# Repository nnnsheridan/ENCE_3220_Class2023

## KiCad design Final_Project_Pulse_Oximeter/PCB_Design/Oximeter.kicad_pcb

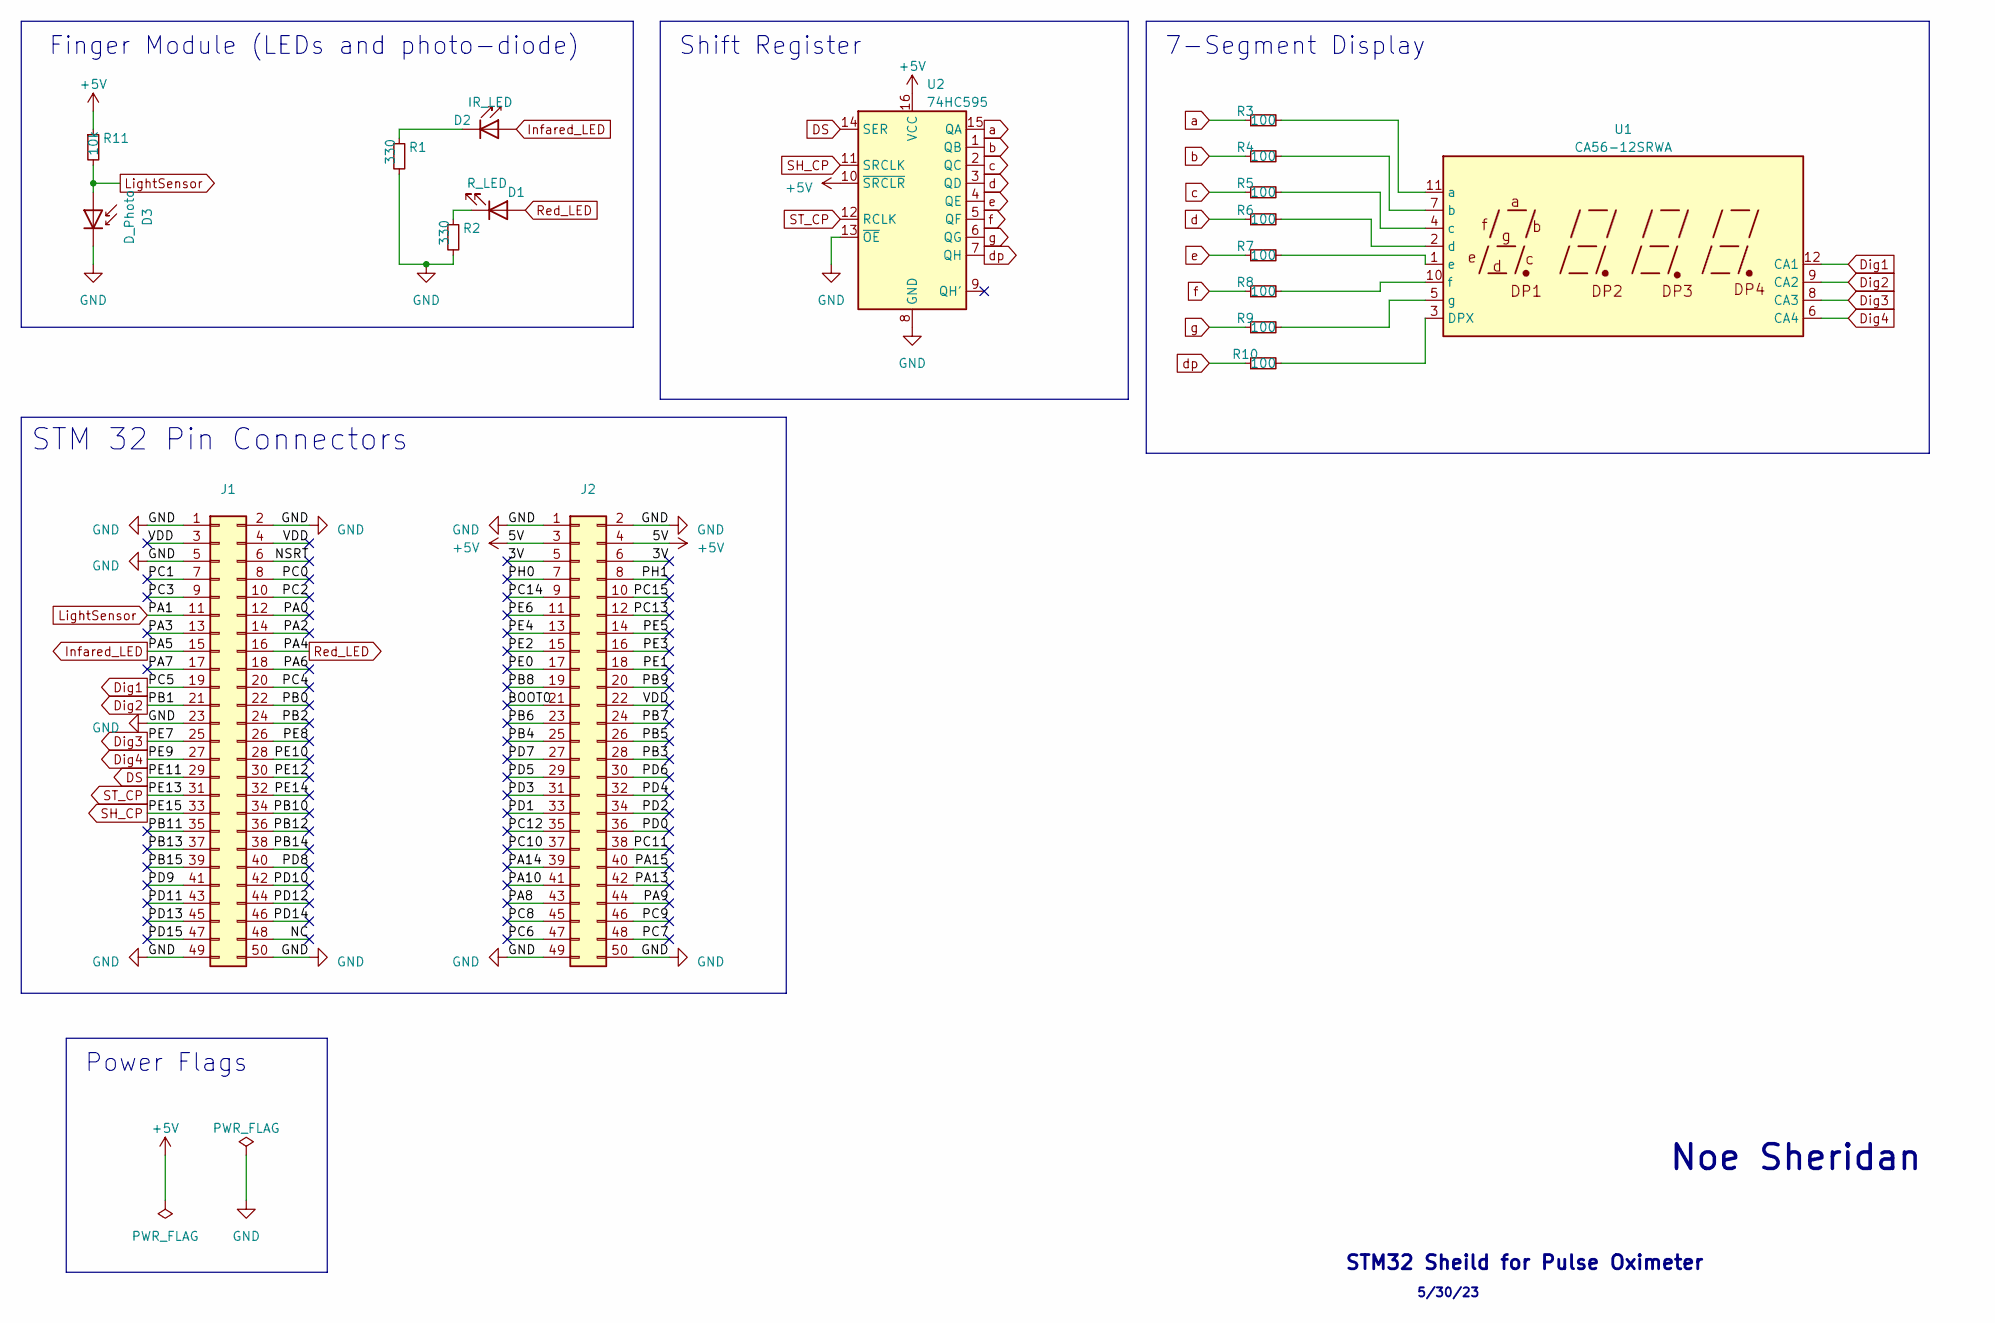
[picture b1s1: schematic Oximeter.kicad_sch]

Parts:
D1: R_LED; LED_D3.0mm
D2: IR_LED; LED_D3.0mm_IRGrey
D3: D_Photo; LED_D3.0mm_IRBlack
J1, J2: Conn_02x25_Odd_Even; PinSocket_2x25_P2.54mm_Vertical
R1, R2: 330; R_0805_2012Metric
R3, R4, R5, R6, R7, R8, R9, R10: 100; R_0805_2012Metric
R11: 10k; R_0805_2012Metric
U1: CA56-12SRWA
U2: 74HC595; HTSSOP-16-1EP_4.4x5mm_P0.65mm_EP3.4x5mm

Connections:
+5V: J2.3, J2.4, R11.1, U2.10 (~SRCLR), U2.16 (VCC)
/3V: J2.5, J2.6
/BOOT0: J2.21
/NC: J1.48
/NSRT: J1.6
/PA0: J1.12
/PA2: J1.14
/PA3: J1.13
/PA6: J1.18
/PA7: J1.17
/PA8: J2.43
/PA9: J2.44
/PA10: J2.41
/PA13: J2.42
/PA14: J2.39
/PA15: J2.40
/PB0: J1.22
/PB2: J1.24
/PB3: J2.28
/PB4: J2.25
/PB5: J2.26
/PB6: J2.23
/PB7: J2.24
/PB8: J2.19
/PB9: J2.20
/PB10: J1.34
/PB11: J1.35
/PB12: J1.36
/PB13: J1.37
/PB14: J1.38
/PB15: J1.39
/PC0: J1.8
/PC1: J1.7
/PC2: J1.10
/PC3: J1.9
/PC4: J1.20
/PC6: J2.47
/PC7: J2.48
/PC8: J2.45
/PC9: J2.46
/PC10: J2.37
/PC11: J2.38
/PC12: J2.35
/PC13: J2.12
/PC14: J2.9
/PC15: J2.10
/PD0: J2.36
/PD1: J2.33
/PD2: J2.34
/PD3: J2.31
/PD4: J2.32
/PD5: J2.29
/PD6: J2.30
/PD7: J2.27
/PD8: J1.40
/PD9: J1.41
/PD10: J1.42
/PD11: J1.43
/PD12: J1.44
/PD13: J1.45
/PD14: J1.46
/PD15: J1.47
/PE0: J2.17
/PE1: J2.18
/PE2: J2.15
/PE3: J2.16
/PE4: J2.13
/PE5: J2.14
/PE6: J2.11
/PE8: J1.26
/PE10: J1.28
/PE12: J1.30
/PE14: J1.32
/PH0: J2.7
/PH1: J2.8
/VDD: J1.3, J1.4, J2.22
DS: J1.29, U2.14 (SER)
Dig1: J1.19, U1.12 (CA1)
Dig2: J1.21, U1.9 (CA2)
Dig3: J1.25, U1.8 (CA3)
Dig4: J1.27, U1.6 (CA4)
GND: D3.1 (K), J1.1, J1.2, J1.5, J1.23, J1.49, J1.50, J2.1, J2.2, J2.49, J2.50, R1.2, R2.2, U2.8 (GND), U2.13 (~OE)
Infared_LED: D2.2 (A), J1.15
LightSensor: D3.2 (A), J1.11, R11.2
unnamed: D1.1 (K), R2.1
unnamed: D2.1 (K), R1.1
unnamed: R10.2, U1.3 (DPX)
unnamed: R3.2, U1.11 (a)
unnamed: R4.2, U1.7 (b)
unnamed: R5.2, U1.4 (c)
unnamed: R6.2, U1.2 (d)
unnamed: R7.2, U1.1 (e)
unnamed: R8.2, U1.10 (f)
unnamed: R9.2, U1.5 (g)
Red_LED: D1.2 (A), J1.16
SH_CP: J1.33, U2.11 (SRCLK)
ST_CP: J1.31, U2.12 (RCLK)
a: R3.1, U2.15 (QA)
b: R4.1, U2.1 (QB)
c: R5.1, U2.2 (QC)
d: R6.1, U2.3 (QD)
dp: R10.1, U2.7 (QH)
e: R7.1, U2.4 (QE)
f: R8.1, U2.5 (QF)
g: R9.1, U2.6 (QG)

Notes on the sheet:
5/30/23
STM 32 Pin Connectors
Finger Module (LEDs and photo-diode)
Noe Sheridan
7-Segment Display
Power Flags
STM32 Sheild for Pulse Oximeter
Shift Register

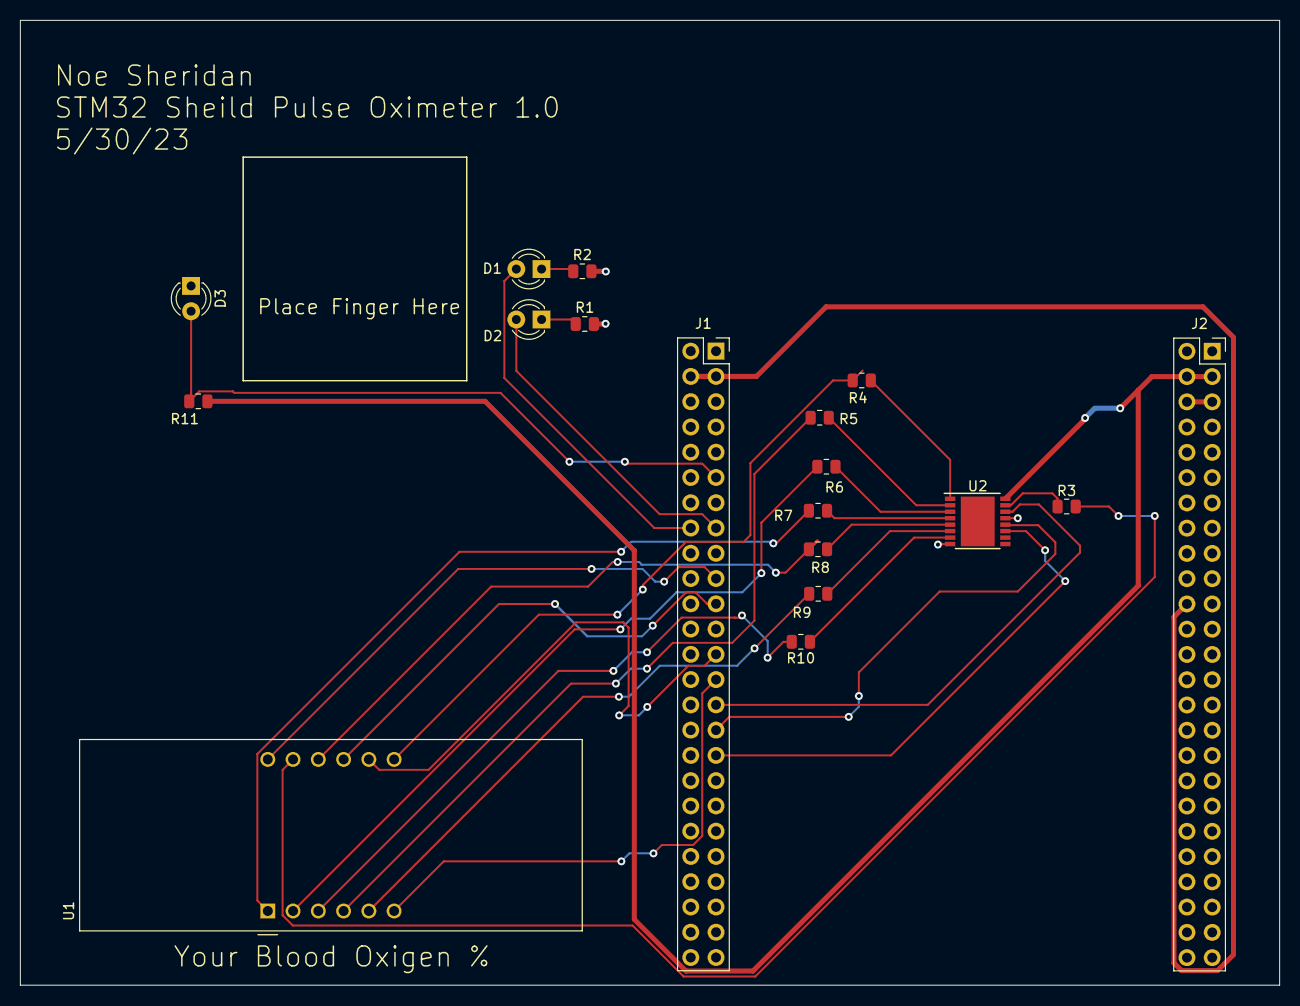
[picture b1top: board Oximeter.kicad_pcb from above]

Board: 2 copper layers, 126.6 x 97.0 mm, 18 parts (0 on the bottom side), 32 nets.

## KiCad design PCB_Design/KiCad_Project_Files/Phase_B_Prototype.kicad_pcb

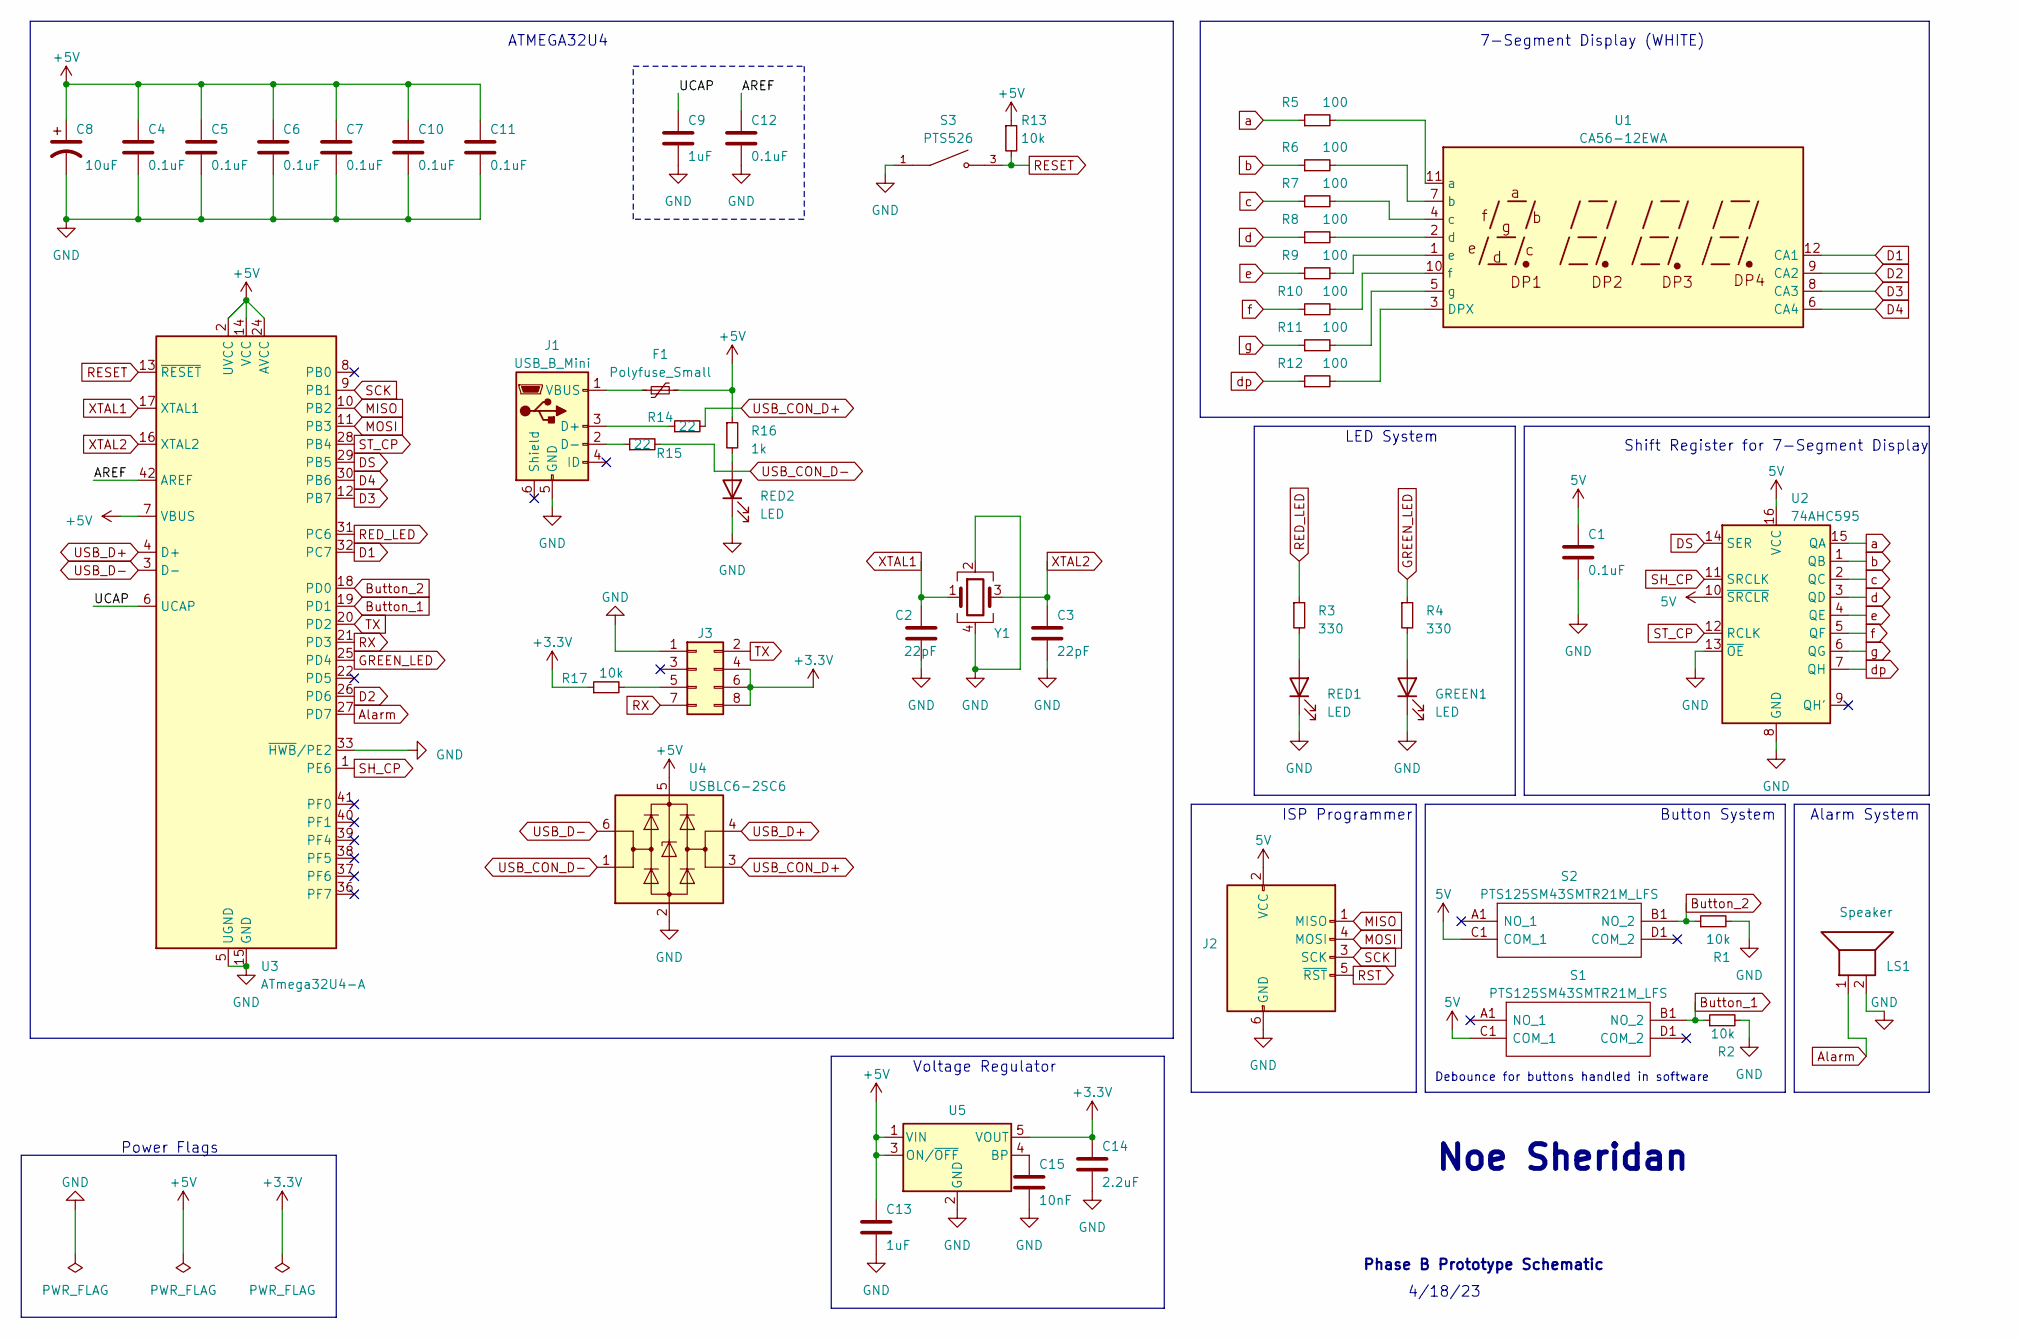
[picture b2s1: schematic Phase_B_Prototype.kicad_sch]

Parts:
C1, C4, C5, C6, C7, C10, C11, C12: 0.1uF; C_0603_1608Metric
C2, C3: 22pF; C_0603_1608Metric
C8: 10uF; C_0805_2012Metric
C9, C13: 1uF; C_0603_1608Metric
C14: 2.2uF; C_0603_1608Metric
C15: 10nF; C_0603_1608Metric
F1: Polyfuse_Small; Fuse_1812_4532Metric
GREEN1: LED; LED_0805_2012Metric
J1: USB_B_Mini; USB_Mini-B_Lumberg_2486_01_Horizontal
J2: AVR-ISP-6; PinSocket_2x03_P2.54mm_Vertical
J3: Conn_02x04_Odd_Even; PinSocket_2x04_P2.54mm_Vertical
LS1: Speaker; Buzzer_12x9.5RM7.6
R1, R2: 10k; R_0805_2012Metric
R3, R4: 330; R_0805_2012Metric
R5, R6, R7, R8, R9, R10, R11, R12: 100; R_0805_2012Metric
R13, R17: 10k; R_0603_1608Metric
R14, R15: 22; R_0603_1608Metric
R16: 1k; R_0603_1608Metric
RED1, RED2: LED; LED_0805_2012Metric
S1, S2: PTS125SM43SMTR21M_LFS; PTS125_SMD_Button; Manufacturer_Part_Number PTS125SM43SMTR21M LFS; Mouser Part Number 611-PTS125S43SMTRLFS
S3: PTS526; PTS526_SMD_Button; PARTREV 20 mar 19
U1: CA56-12EWA
U2: 74AHC595; TSSOP-16_4.4x5mm_P0.65mm
U3: ATmega32U4-A; TQFP-44_10x10mm_P0.8mm
U4: USBLC6-2SC6; SOT-23-6
U5: LP2985-3.3; SOT-23-5
Y1: Crystal_GND24; Crystal_SMD_Abracon_ABM8G-4Pin_3.2x2.5mm

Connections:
+3.3V: C14.1, J3.4, J3.6, J3.8, R17.1, U5.5 (VOUT)
+5V: C4.1, C5.1, C6.1, C7.1, C8.1, C10.1, C11.1, C13.1, F1.2, R13.1, R16.1, U3.2 (UVCC), U3.7 (VBUS), U3.14 (VCC), U3.24 (AVCC), U3.34 (VCC), U3.44 (AVCC), U4.5 (VBUS), U5.1 (VIN), U5.3 (ON/~OFF)
/AREF: C12.1, U3.42 (AREF)
/UCAP: C9.1, U3.6 (UCAP)
Alarm: LS1.1, U3.27 (PD7)
Button_1: R2.1, S1.B1 (NO_2), U3.19 (PD1)
Button_2: R1.1, S2.B1 (NO_2), U3.18 (PD0)
D1: U1.12 (CA1), U3.32 (PC7)
D2: U1.9 (CA2), U3.26 (PD6)
D3: U1.8 (CA3), U3.12 (PB7)
D4: U1.6 (CA4), U3.30 (PB6)
DS: U2.14 (SER), U3.29 (PB5)
GND: C1.2, C2.2, C3.2, C4.2, C5.2, C6.2, C7.2, C8.2, C9.2, C10.2, C11.2, C12.2, C13.2, C14.2, C15.2, GREEN1.1 (K), J1.5 (GND), J2.6 (GND), J3.1, LS1.2, R1.2, R2.2, RED1.1 (K), RED2.1 (K), S3.1, U2.8 (GND), U2.13 (~OE), U3.5 (UGND), U3.15 (GND), U3.23 (GND), U3.33 (~HWB/PE2), U3.35 (GND), U3.43 (GND), U4.2 (GND), U5.2 (GND), Y1.2, Y1.4
GREEN_LED: R4.1, U3.25 (PD4)
MISO: J2.1 (MISO), U3.10 (PB2)
MOSI: J2.4 (MOSI), U3.11 (PB3)
unnamed: GREEN1.2 (A), R4.2
unnamed: J1.3 (D+), R14.1
unnamed: J1.2 (D-), R15.1
unnamed: F1.1, J1.1 (VBUS)
unnamed: J3.5, R17.2
unnamed: R3.2, RED1.2 (A)
unnamed: R16.2, RED2.2 (A)
unnamed: R12.2, U1.3 (DPX)
unnamed: R5.2, U1.11 (a)
unnamed: R6.2, U1.7 (b)
unnamed: R7.2, U1.4 (c)
unnamed: R8.2, U1.2 (d)
unnamed: R9.2, U1.1 (e)
unnamed: R10.2, U1.10 (f)
unnamed: R11.2, U1.5 (g)
unnamed: C15.1, U5.4 (BP)
RED_LED: R3.1, U3.31 (PC6)
RESET: R13.2, S3.3, U3.13 (~RESET)
RST: J2.5 (~RST)
RX: J3.7, U3.21 (PD3)
SCK: J2.3 (SCK), U3.9 (PB1)
SH_CP: U2.11 (SRCLK), U3.1 (PE6)
ST_CP: U2.12 (RCLK), U3.28 (PB4)
TX: J3.2, U3.20 (PD2)
USB_CON_D+: R14.2, U4.3 (I/O2)
USB_CON_D-: R15.2, U4.1 (I/O1)
USB_D+: U3.4 (D+), U4.4 (I/O2)
USB_D-: U3.3 (D-), U4.6 (I/O1)
VDC: C1.1, J2.2 (VCC), S1.C1 (COM_1), S2.C1 (COM_1), U2.10 (~SRCLR), U2.16 (VCC)
XTAL1: C2.1, U3.17 (XTAL1), Y1.1
XTAL2: C3.1, U3.16 (XTAL2), Y1.3
a: R5.1, U2.15 (QA)
b: R6.1, U2.1 (QB)
c: R7.1, U2.2 (QC)
d: R8.1, U2.3 (QD)
dp: R12.1, U2.7 (QH)
e: R9.1, U2.4 (QE)
f: R10.1, U2.5 (QF)
g: R11.1, U2.6 (QG)

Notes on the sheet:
Alarm System
LED System
Shift Register for 7-Segment Display
ATMEGA32U4
Power Flags
Voltage Regulator
Phase B Prototype Schematic
4/18/23
7-Segment Display (WHITE)
Noe Sheridan
Debounce for buttons handled in software
Button System
ISP Programmer

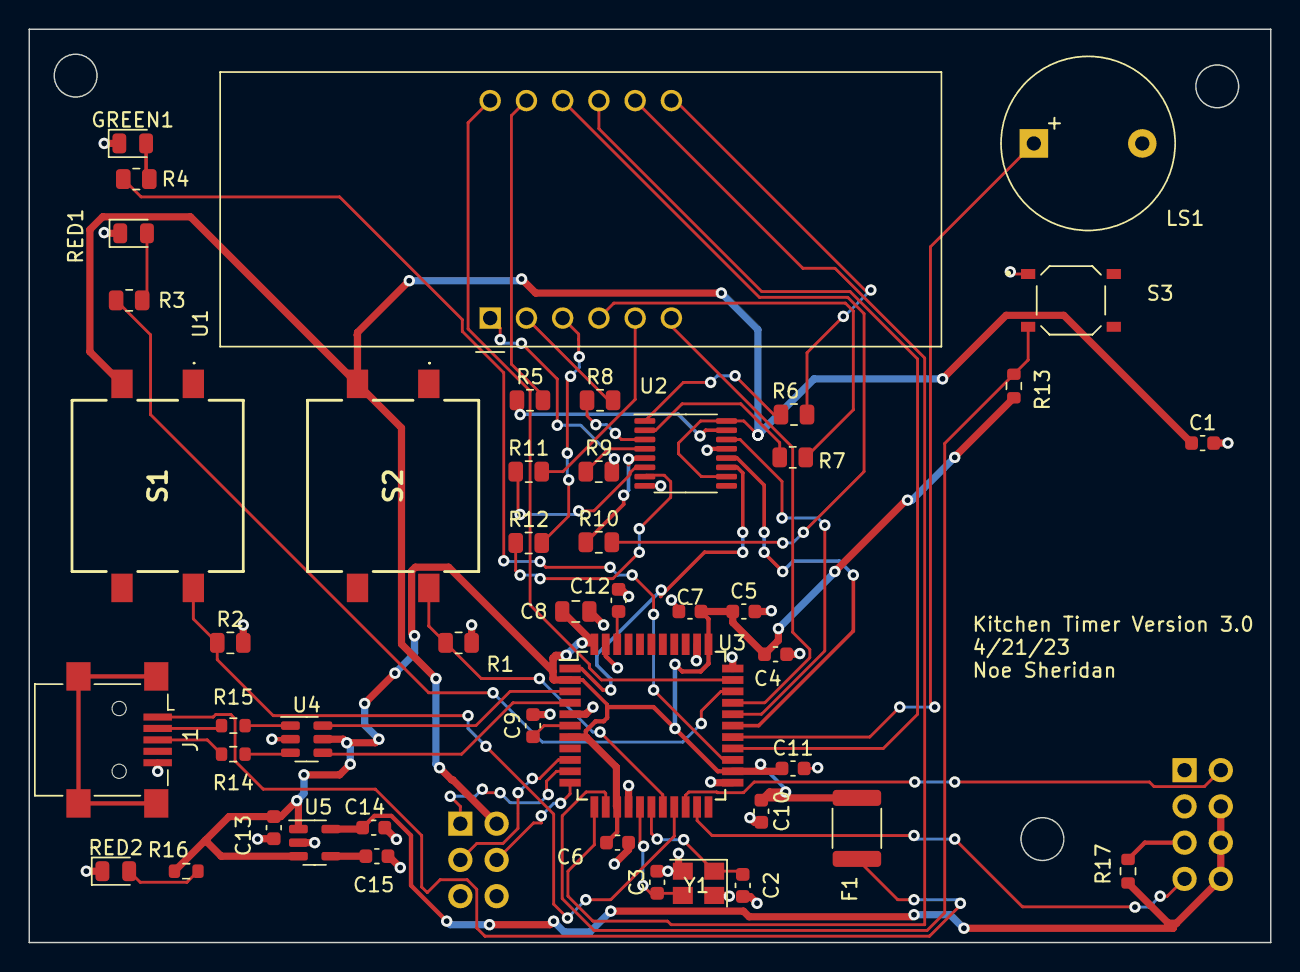
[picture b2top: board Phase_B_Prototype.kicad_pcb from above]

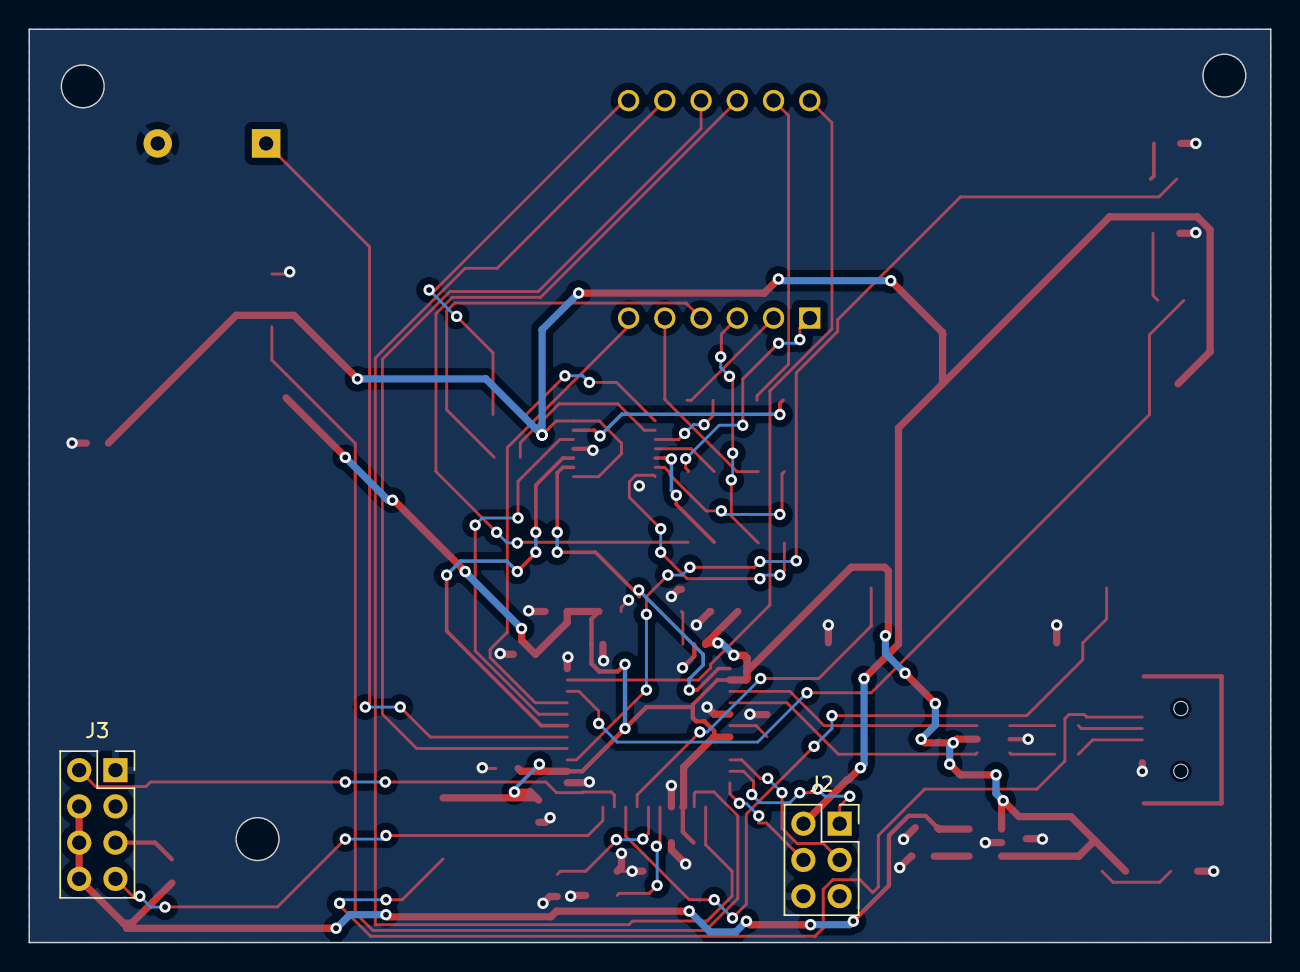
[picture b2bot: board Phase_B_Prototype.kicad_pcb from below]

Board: 2 copper layers, 87.0 x 64.0 mm, 49 parts (2 on the bottom side), 54 nets.

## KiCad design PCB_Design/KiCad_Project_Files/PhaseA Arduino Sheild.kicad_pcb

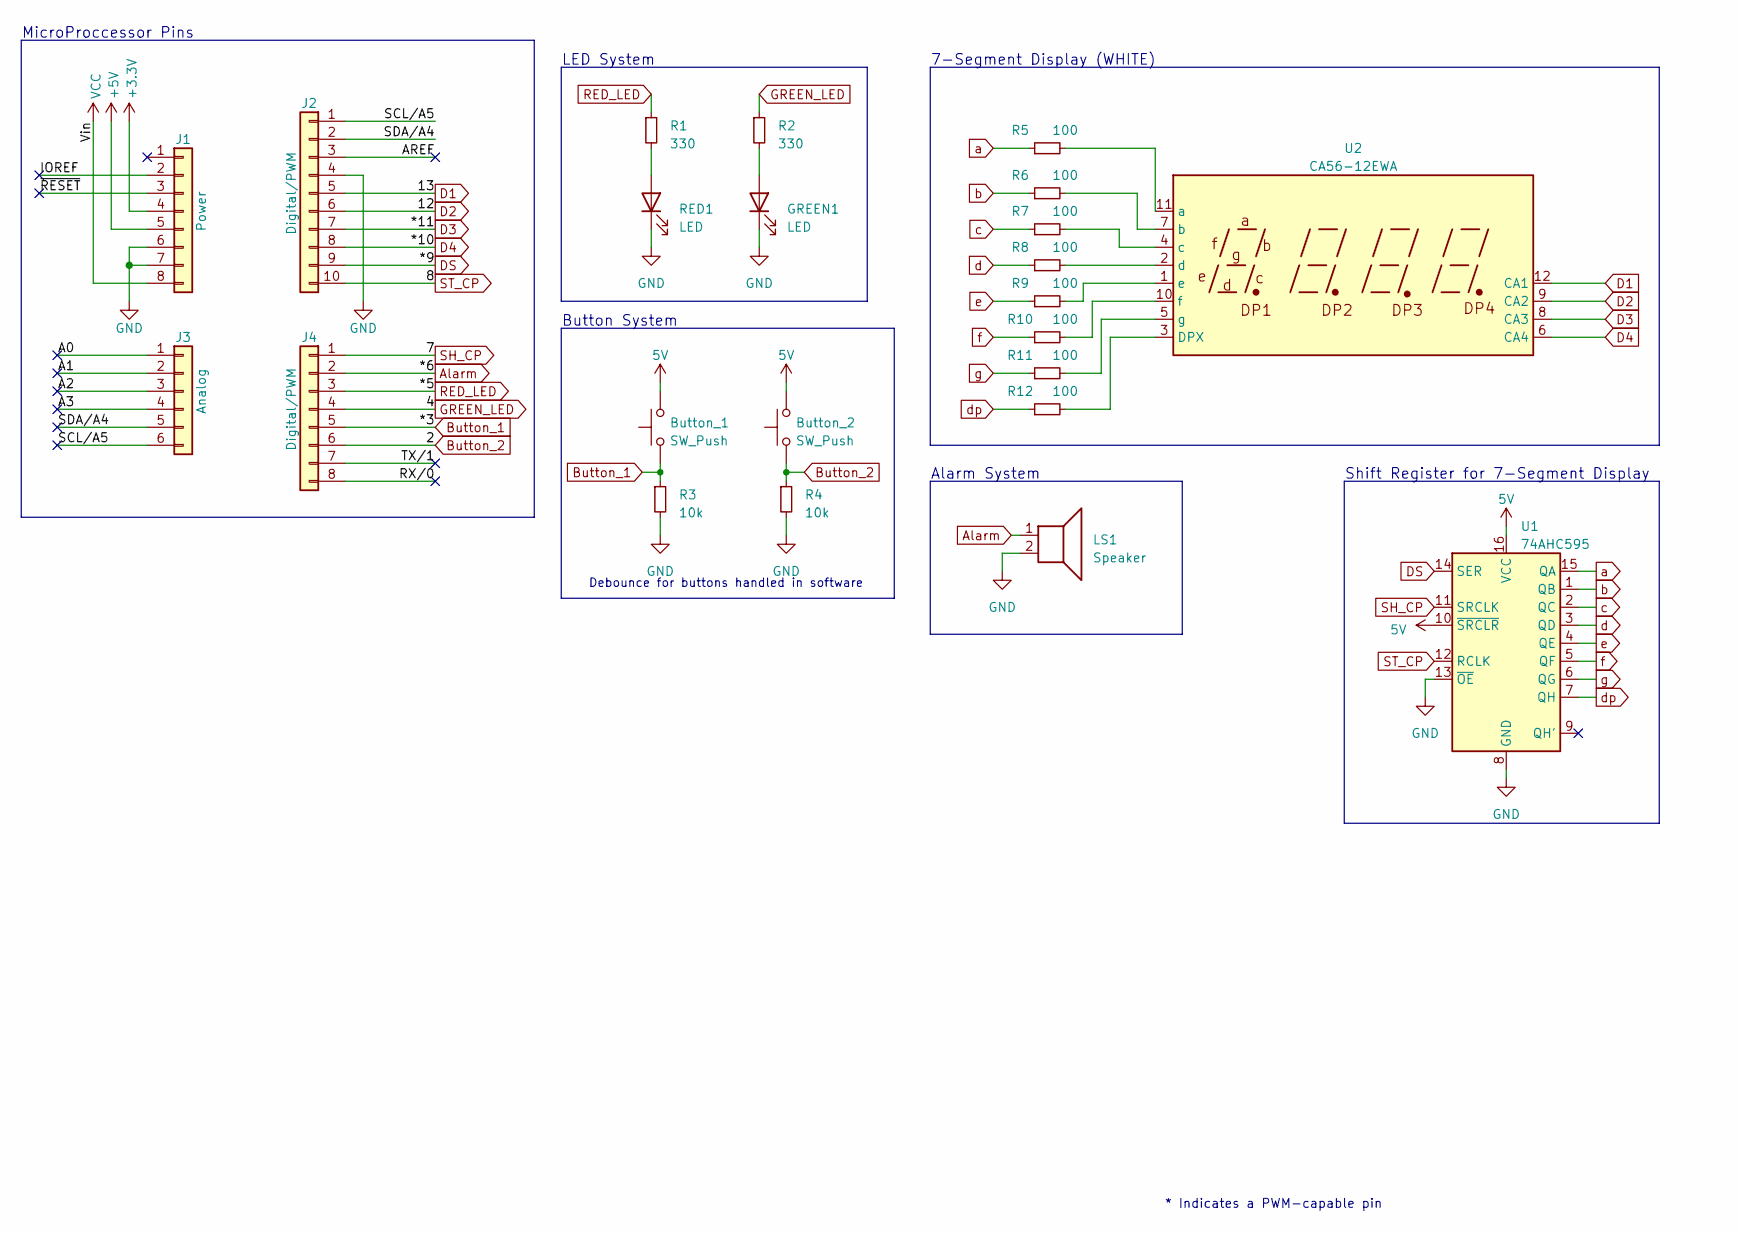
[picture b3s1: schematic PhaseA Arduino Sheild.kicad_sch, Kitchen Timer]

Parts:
Button_1, Button_2: SW_Push; SW_PUSH_6mm
GREEN1: LED; LED_D5.0mm
J1: Power; PinSocket_1x08_P2.54mm_Vertical
J2: Digital/PWM; PinSocket_1x10_P2.54mm_Vertical
J3: Analog; PinSocket_1x06_P2.54mm_Vertical
J4: Digital/PWM; PinSocket_1x08_P2.54mm_Vertical
LS1: Speaker; Buzzer_12x9.5RM7.6
R1, R2: 330; R_Axial_DIN0204_L3.6mm_D1.6mm_P7.62mm_Horizontal
R3, R4: 10k; R_Axial_DIN0204_L3.6mm_D1.6mm_P7.62mm_Horizontal
R5, R6, R7, R8, R9, R10, R11, R12: 100; R_Axial_DIN0204_L3.6mm_D1.6mm_P7.62mm_Horizontal
RED1: LED; LED_D5.0mm
U1: 74AHC595; DIP-16_W7.62mm_LongPads
U2: CA56-12EWA

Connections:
+3V3: J1.4
+5V: J1.5
/A0: J3.1
/A1: J3.2
/A2: J3.3
/A3: J3.4
/AREF: J2.3
/IOREF: J1.2
/RX/0: J4.8
/SCL/A5: J2.1, J3.6
/SDA/A4: J2.2, J3.5
/TX/1: J4.7
/~RESET: J1.3
Alarm: J4.2, LS1.1
Button_1: Button_1.1, J4.5, R3.1
Button_2: Button_2.1, J4.6, R4.1
D1: J2.5, U2.12 (CA1)
D2: J2.6, U2.9 (CA2)
D3: J2.7, U2.8 (CA3)
D4: J2.8, U2.6 (CA4)
DS: J2.9, U1.14 (SER)
GND: GREEN1.1 (K), J1.6, J1.7, J2.4, LS1.2, R3.2, R4.2, RED1.1 (K), U1.8 (GND), U1.13 (~OE)
GREEN_LED: J4.4, R2.1
unnamed: GREEN1.2 (A), R2.2
unnamed: R1.2, RED1.2 (A)
unnamed: R12.2, U2.3 (DPX)
unnamed: R5.2, U2.11 (a)
unnamed: R6.2, U2.7 (b)
unnamed: R7.2, U2.4 (c)
unnamed: R8.2, U2.2 (d)
unnamed: R9.2, U2.1 (e)
unnamed: R10.2, U2.10 (f)
unnamed: R11.2, U2.5 (g)
RED_LED: J4.3, R1.1
SH_CP: J4.1, U1.11 (SRCLK)
ST_CP: J2.10, U1.12 (RCLK)
VCC: J1.8
VDC: Button_1.2, Button_2.2, U1.10 (~SRCLR), U1.16 (VCC)
a: R5.1, U1.15 (QA)
b: R6.1, U1.1 (QB)
c: R7.1, U1.2 (QC)
d: R8.1, U1.3 (QD)
dp: R12.1, U1.7 (QH)
e: R9.1, U1.4 (QE)
f: R10.1, U1.5 (QF)
g: R11.1, U1.6 (QG)

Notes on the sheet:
Alarm System
Shift Register for 7-Segment Display
MicroProccessor Pins
Button System
* Indicates a PWM-capable pin
LED System
7-Segment Display (WHITE)
Debounce for buttons handled in software

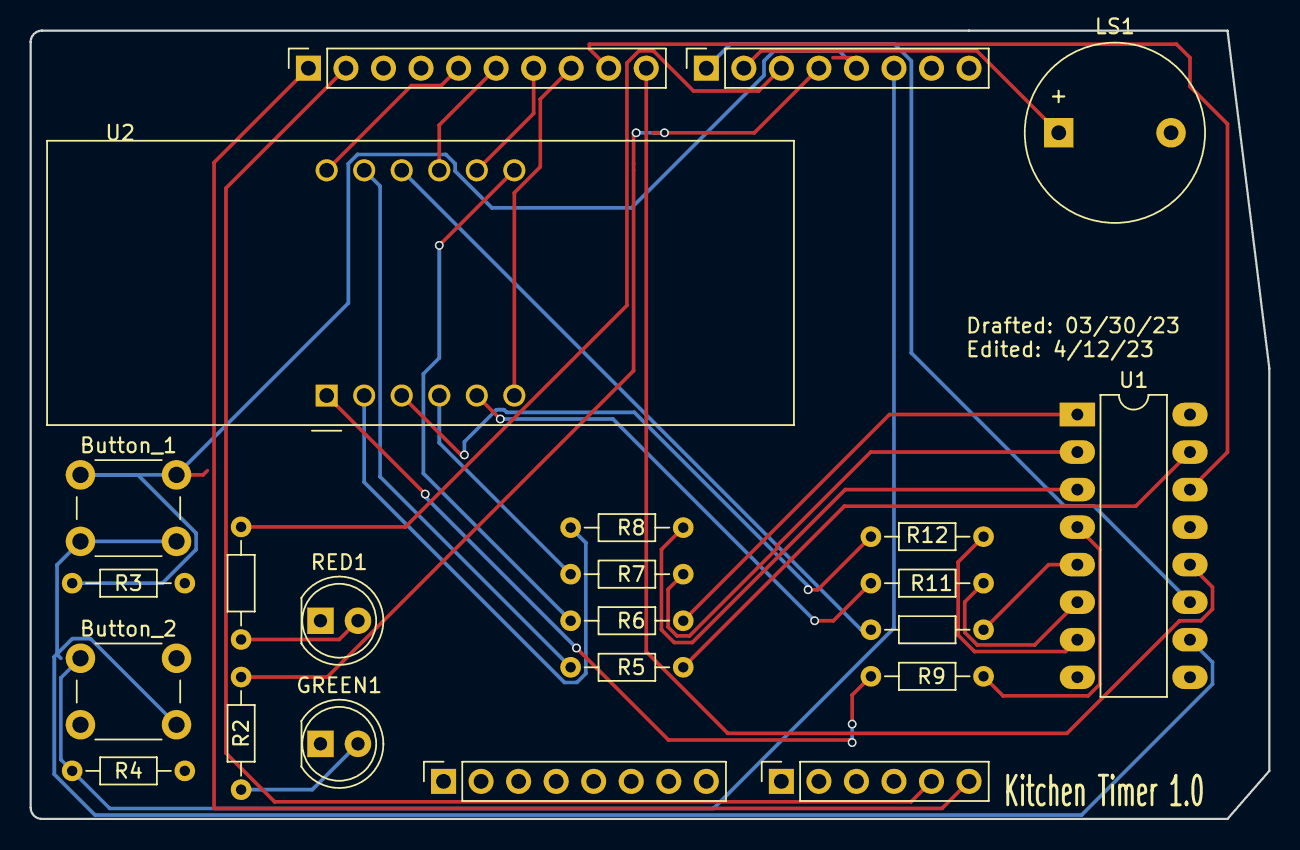
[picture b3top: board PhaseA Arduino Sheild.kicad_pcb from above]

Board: 2 copper layers, 83.8 x 53.3 mm, 23 parts (0 on the bottom side), 34 nets.

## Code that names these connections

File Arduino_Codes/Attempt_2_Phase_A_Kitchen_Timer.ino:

/* Code Written by Noe Sheridan with the help and reference of Goncalo Martins' Code template "Clock_v2_1"
Also with the input of Jon McHorse
Original File Created: 4-04-2023
Latest Edit: 4-13-2023
Edits include: adding edited portionsof Dr. Martins' "Clock_v2_1" to implement the Buzzer and ensure that the timer can be started and stopped with the LED display integrated. 

*/


#define BUTTON_2  2 //increase timer
#define BUTTON_1  3 //start/stop 
#define RED_LED   5
#define GREEN_LED 4
#define BUZZER    6

#define DATA      9 // DS
#define LATCH     8 // ST_CP
#define CLOCK     7 // SH_CP

#define DIGIT_4   10
#define DIGIT_3   11
#define DIGIT_2   12
#define DIGIT_1   13

unsigned char table[]=
{0x3f,0x06,0x5b,0x4f,0x66,0x6d,0x7d,0x07,0x7f,0x6f,0x77,0x7c
,0x39,0x5e,0x79,0x71,0x00};
byte gCurrentDigit;

// Volatile Variables
volatile unsigned char BuzzerFlag = 0;
volatile unsigned char isr_1_flag = 0;
volatile unsigned char isr_2_flag = 0;
volatile unsigned char isr_3_flag = 0;


// Timer Variables
#define DEFAULT_COUNT 45     // default value is 30secs
volatile int  count = DEFAULT_COUNT;
unsigned char timer_running = 0; 

unsigned int reload_timer_1 = 62500; // corresponds to 1 second
byte         reload_timer_2 = 10;  // display refresh time
/**
 * @brief Setup peripherals and timers
 * @param
 * @return
 */
void setup() {
  // LEDs Pins
  pinMode(RED_LED, OUTPUT);
  pinMode(GREEN_LED, OUTPUT);

  // LEDs -> Timer Stopped
  digitalWrite(RED_LED, HIGH);
  digitalWrite(GREEN_LED, HIGH);

  // Button Pins
  pinMode(BUTTON_1, INPUT_PULLUP);
  attachInterrupt(digitalPinToInterrupt(BUTTON_1), Button_1_ISR, RISING);
  pinMode(BUTTON_2, INPUT_PULLUP);
  attachInterrupt(digitalPinToInterrupt(BUTTON_2), Button_2_ISR, RISING);

  // Buzer Pins
  pinMode(BUZZER, OUTPUT);

  // Buzzer -> Off
  digitalWrite(BUZZER,LOW);

  // 7-Seg Display
  pinMode(DIGIT_1, OUTPUT);
  pinMode(DIGIT_2, OUTPUT);
  pinMode(DIGIT_3, OUTPUT);
  pinMode(DIGIT_4, OUTPUT);

  // Shift Register Pins
  pinMode(LATCH, OUTPUT);
  pinMode(CLOCK, OUTPUT);
  pinMode(DATA, OUTPUT);

  disp_off();  // turn off the display

  // Initialize Timer1 (16bit) -> Used for clock
  // Speed of Timer1 = 16MHz/256 = 62.5 KHz
  //startTimer1(); // this is done using the start button

  // Initialize Timer2 (8bit) -> Used to refresh display
  // Speed of Timer2 = 16MHz/1024 = 15.625 KHz
  TCCR2A = 0;
  TCCR2B = 0;
  OCR2A = reload_timer_2;                     // max value 2^8 - 1 = 255
  TCCR2A |= (1<<WGM21);
  TCCR2B = (1<<CS22) | (1<<CS21) | (1<<CS20); // 1204 prescaler
  TIMSK2 |= (1<<OCIE2A);
  interrupts();                             
}


/**
 * @brief Shifts the bits through the shift register
 * @param num
 * @param dp
 * @return
 */
void display(unsigned char num, unsigned char dp)
{
  digitalWrite(LATCH, LOW);
  shiftOut(DATA, CLOCK, MSBFIRST, table[num] | (dp<<7));
  digitalWrite(LATCH, HIGH);
}

/**
 * @brief Turns the 7-seg display off
 * @param
 * @return
 */

void disp_off(){
   digitalWrite(DIGIT_1, HIGH);
   digitalWrite(DIGIT_2, HIGH);
   digitalWrite(DIGIT_3, HIGH);
   digitalWrite(DIGIT_4, HIGH);
}

/*
void disp_on(){
   digitalWrite(DIGIT_1, LOW);
   digitalWrite(DIGIT_2, LOW);
   digitalWrite(DIGIT_3, LOW);
   digitalWrite(DIGIT_4, LOW);
}*/

/**
 * @brief Button 2 ISR
 * @param
 * @return
 */
void Button_2_ISR()
{ 
  // Set ISR Flag
  count++;
}


/**
 * @brief Button 1 ISR
 * @param
 * @return
 */
void Button_1_ISR()
{
  // Set ISR Flag
  isr_1_flag = 1;
}


/**
 * @brief Timer 2 ISR
 * @param TIMER2_COMPA_vect
 * @return
 */
ISR(TIMER2_COMPA_vect)   // Timer2 interrupt service routine (ISR)
{
  disp_off();  // turn off the display
  OCR2A = reload_timer_2;  // load timer
 
  switch (gCurrentDigit)
  {
    case 1: //0x:xx
      display( int((count/60) / 10) % 6, 0 );   // prepare to display digit 1 (most left)
      digitalWrite(DIGIT_1, LOW);  // turn on digit 1
      break;
 
    case 2: //x0:xx
      display( int(count / 60) % 10, 1 );   // prepare to display digit 2
      digitalWrite(DIGIT_2, LOW);     // turn on digit 2
      break;
 
    case 3: //xx:0x
      display( (count / 10) % 6, 0 );   // prepare to display digit 3
      digitalWrite(DIGIT_3, LOW);    // turn on digit 3
      break;
 
    case 4: //xx:x0
      display(count % 10, 0); // prepare to display digit 4 (most right)
      digitalWrite(DIGIT_4, LOW);  // turn on digit 4
      break;

    default:
      break;
  }
 
  gCurrentDigit = (gCurrentDigit % 4) + 1;
}


/**
 * @brief Timer 1 ISR
 * @param TIMER1_COMPA_vect
 * @return
 */
ISR(TIMER1_COMPA_vect)  // Timer1 interrupt service routine (ISR)
{
  count--;
  OCR1A = reload_timer_1;

  if(count == 0)
  {
      // Stop Timer
      stopTimer1();
      
      // Raise Alarm
      BuzzerFlag = 1;
      timer_running = 0;
  }
}

/**
 * @brief Stop Timer 1
 * @param
 * @return
 */
void stopTimer1()
{
  // Stop Timer
  TCCR1B = 0; // stop clock
  TIMSK1 = 0; // cancel clock timer interrupt
}

/**
 * @brief Start Timer 1
 * @param
 * @return
 */
void startTimer1()
{
  // Initialize Timer1 (16bit) -> Used for clock
  // Speed of Timer1 = 16MHz/256 = 62.5 KHz
  noInterrupts();
  TCCR1A = 0;
  TCCR1B = 0;
  OCR1A = reload_timer_1; // compare match register 16MHz/256
  TCCR1B |= (1<<WGM12);   // CTC mode
  TCCR1B |= (1<<CS12);    // 256 prescaler 
  TIMSK1 |= (1<<OCIE1A);  // enable timer compare interrupt
  interrupts();
}

/**
 * @brief Turn On Buzzer
 * @param
 * @return
 */
void activeBuzzer()
{
  unsigned char i;
  unsigned char sleepTime = 1; // ms
  
  for(i=0;i<100;i++)
  {
    digitalWrite(BUZZER,HIGH);
    delay(sleepTime);//wait for 1ms
    digitalWrite(BUZZER,LOW);
    delay(sleepTime);//wait for 1ms
  }
}



/**
 * @brief Main Loop
 * @param
 * @return
 */
void loop() 
{ 
  // Combination of Pooling and Interrupt

  // Attend Button 1
  if(isr_1_flag == 1)
  {
    // Reset ISR Flag
    isr_1_flag = 0;

    // Code
    if(timer_running == 0)
    {
      // Start Timer
      timer_running = 1;

      if(count == 0)
        count = DEFAULT_COUNT;

      if(BuzzerFlag == 1)
      {
        BuzzerFlag = 0;

        // LEDs -> Timer Stopped
        digitalWrite(RED_LED, HIGH);
        digitalWrite(GREEN_LED, HIGH);
      }
      else
      {
        startTimer1();
        // LEDs -> Timer Running
        digitalWrite(RED_LED, LOW);
        digitalWrite(GREEN_LED, HIGH);
      }
    }
    else
    {
      // Stop Timer
      stopTimer1();
      timer_running = 0;

      // LEDs -> Timer Running
      digitalWrite(RED_LED, HIGH);
      digitalWrite(GREEN_LED, HIGH);
    }
  }

  // Attend gBuzzerFlag
  if(BuzzerFlag == 1)
  {
    // Make Noise...
    digitalWrite(RED_LED, HIGH);
    digitalWrite(GREEN_LED, LOW);
    activeBuzzer();
  }
    
}

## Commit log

2023-04-13 files added
2023-04-13 Added folder with Arduino Codes
2023-04-13 Added folder and placed files within
2023-04-13 Created Folder and placed KiCAD files within
2023-04-21 Phase B part Alpha. PCB files uploaded.
2023-05-04 Git Commit
2023-06-01 Final Project Commit
2023-06-01 First Version of STM32 Codes, without communication to the 7-segment display
2023-06-01 Updated Gerber Files, and added Prototype build photo
2023-06-01 Added presentation and final code
2023-06-06 Assembly process of Physical PCB
2023-06-08 Final Beta release and final updates to all files
